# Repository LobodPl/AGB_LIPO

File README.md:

# README AGB_LIPO from makhowastaken

LiPo adapter for Game Boy Advance.

* Uses these battery terminals: https://www.aliexpress.com/item/32946601230.html
* a standard TP4056 module (Micro USB or USB C): https://www.aliexpress.com/item/32649780468.html
* and pretty much whatever diode you can get your hands on: https://www.aliexpress.com/item/32664545131.html

I got my boards in and had to make some alterations to get them to fit better. I'm still waiting on the terminals so I'll add a youtube video for instruction when I get everything in.
# My Project README

## Order at OSHPARK: https://oshpark.com/shared_projects/AJPIjHIz

## Front:

* Solder TP1 to VIN+ of TP4056
## Back:

# Symbols
* U1 - TP4056(Have to be soldered UpsideDown)
  https://aliexpress.com/item/32649780468.html (0,41$)
* U2 - TPS3700DDCR (Texas Intruments)
  https://mouser.com/ProductDetail/Texas-Instruments/TPS3700DDCR?qs=mNuCSSXMdBz5rDLbdTsfrQ%3D%3D (1,79$)
* IC1 - LP38693MP-ADJ (Texas Intruments)
  https://mouser.com/ProductDetail/Texas-Instruments/LP38693MP-ADJ-NOPB?qs=%2Fha2pyFaduhxATx%252BYNp3uIz3XjGhpXqCpbQ80pAe8SqAsUaeuhDVzOCKiaIvHl6%2F (1,45$)
* D1,D2 - SS14 Schottky Diode (or silmilar schottky diode)
  https://mouser.com/ProductDetail/ON-Semiconductor-Fairchild/SS14?qs=mVVXn4M53U%252BvrBaFv5vr4w%3D%3D (0,76$)
* C1,C2,C3 - 10u CERAMIC(0603)
  https://mouser.com/ProductDetail/Taiyo-Yuden/JMK107ABJ106KAHT?qs=sGAEpiMZZMuMW9TJLBQkXhrP50NC0Yj7qpkxl5d0wRM%3D (1$)
* C4 - 220u TANTALUM(KEMET-B)
  https://mouser.com/ProductDetail/Vishay-Sprague/TR3B106K010C1000?qs=l4Gc20tDgJLwalMJRLTcCw%3D%3D (1,08$)
* R1 - 470K(0603)
  https://mouser.com/ProductDetail/Panasonic/ERJ-UP3J474V?qs=sGAEpiMZZMtlubZbdhIBINZyO39%252BOXIfR2tJtCQBH%2FQ%3D (0,18$)
* R2 - 62K(0805)
  https://mouser.com/ProductDetail/Panasonic/ERJ-6RBD6202V?qs=sGAEpiMZZMtlubZbdhIBIAseYdsNAjdpz1c9XO5OoSg%3D (0,14$)
* R3 - 1M(0603)
  https://mouser.com/ProductDetail/Panasonic/ERJ-UP3D1004V?qs=sGAEpiMZZMtlubZbdhIBINZyO39%252BOXIfwSlLGtGqBNU%3D (0,35$)
* R4,R5 - 240K(0805)
  https://mouser.com/ProductDetail/Panasonic/ERJ-PB6B2403V?qs=sGAEpiMZZMtlubZbdhIBIMNI7sOfyRuJn5D0R%252BVWI38%3D (0,72$)
* BT1 - 103048 LiPo Cell
  https://pl.aliexpress.com/item/33000132990.html (3$)
# Cost

  PCB manufacturing costs: **2$** on JLCPCB or **9$** on OSHPARK.
  
  This project with **JLCPCB** will cost you ~13$.
  
  With **OSHPARK** you will pay ~20$.

# My Changes

* Load Sharing.
* Voltage Regulation to 3V.
* GBA Low Battery Light trigered at LiPo 3,4V.

# CHANGELOG
## >28.04.2020
* Base concept.

## 28.04.2020
* Added 3.3V Regulator.

## 29.04.2020
* Fixed Regulator capacitors.

## 01.05.2020
* Full circuit redesign.

## 01.06.2020
* One more full circuit redesign.

## 17.06.2020
* Finall release. PCB is now working corectly.

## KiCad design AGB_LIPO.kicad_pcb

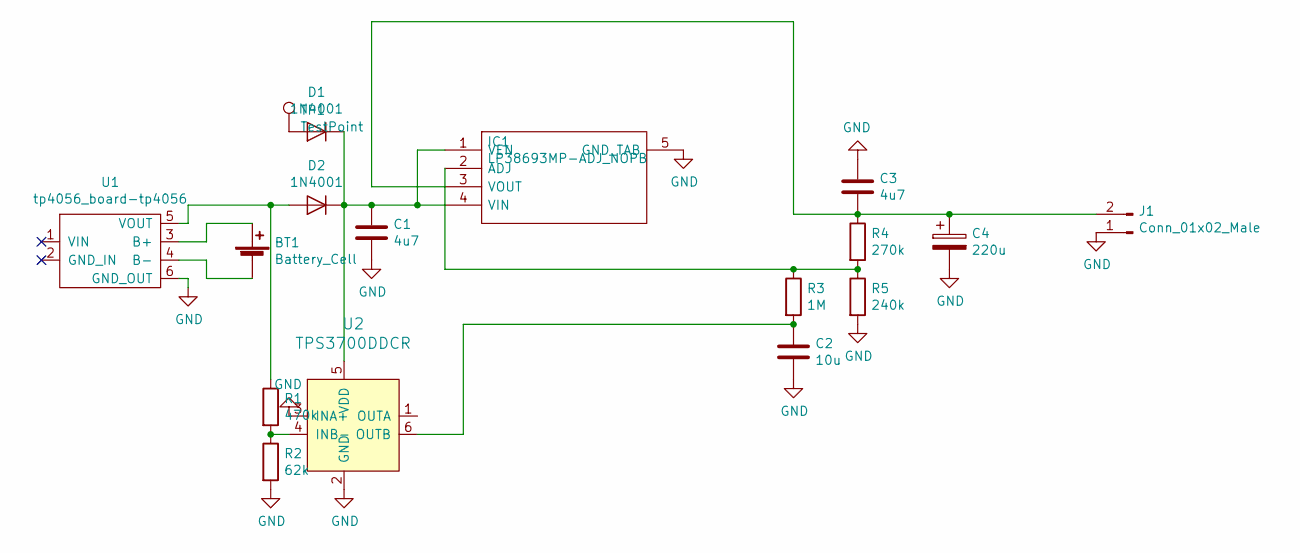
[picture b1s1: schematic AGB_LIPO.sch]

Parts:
BT1: Battery_Cell; PinHeader_1x02_P2.54mm_Vertical
C1, C3: 4u7; C_0603_1608Metric_Pad1.05x0.95mm_HandSolder
C2: 10u; C_0603_1608Metric_Pad1.05x0.95mm_HandSolder
C4: 220u; CP_EIA-3528-21_Kemet-B_Pad1.50x2.35mm_HandSolder
D1, D2: 1N4001; DIOM5626X245N
IC1: LP38693MP-ADJ_NOPB; SOT150P700X180-5N; Manufacturer_Part_Number LP38693MP-ADJ/NOPB; Mouser Part Number 926-LP38693MPADJNOPB
J1: Conn_01x02_Male; TestPoint_2Pads_Pitch2.54mm_Drill0.8mm
R1: 470k; R_0603_1608Metric_Pad1.05x0.95mm_HandSolder
R2: 62k; R_0805_2012Metric_Pad1.15x1.40mm_HandSolder
R3: 1M; R_0603_1608Metric_Pad1.05x0.95mm_HandSolder
R4: 270k; R_0805_2012Metric_Pad1.15x1.40mm_HandSolder
R5: 240k; R_0805_2012Metric_Pad1.15x1.40mm_HandSolder
TP1: TestPoint; TestPoint_Loop_D1.80mm_Drill1.0mm_Beaded
U1: tp4056_board-tp4056; 4056E_LiIon_loader
U2: TPS3700DDCR; SOT98P280X110-6N; MPN TPS3700DDCR; Digi-Key_PN 296-30395-1-ND

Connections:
GND: C1.2, C2.2, C3.1, C4.2, IC1.5 (GND_TAB), J1.1, R2.2, R5.2, U1.6 (GND_OUT), U2.2 (GND), U2.3 (INA+)
unnamed: BT1.1 (+), U1.3 (B+)
unnamed: BT1.2 (-), U1.4 (B-)
unnamed: C1.1, D1.1 (K), D2.1 (K), IC1.1 (VEN), IC1.4 (VIN), U2.5 (VDD)
unnamed: C2.1, R3.2, U2.6 (OUTB)
unnamed: C3.2, C4.1, IC1.3 (VOUT), J1.2, R4.1
unnamed: D1.2 (A), TP1.1
unnamed: D2.2 (A), R1.1, U1.5 (VOUT)
unnamed: IC1.2 (ADJ), R3.1, R4.2, R5.1
unnamed: R1.2, R2.1, U2.4 (INB-)

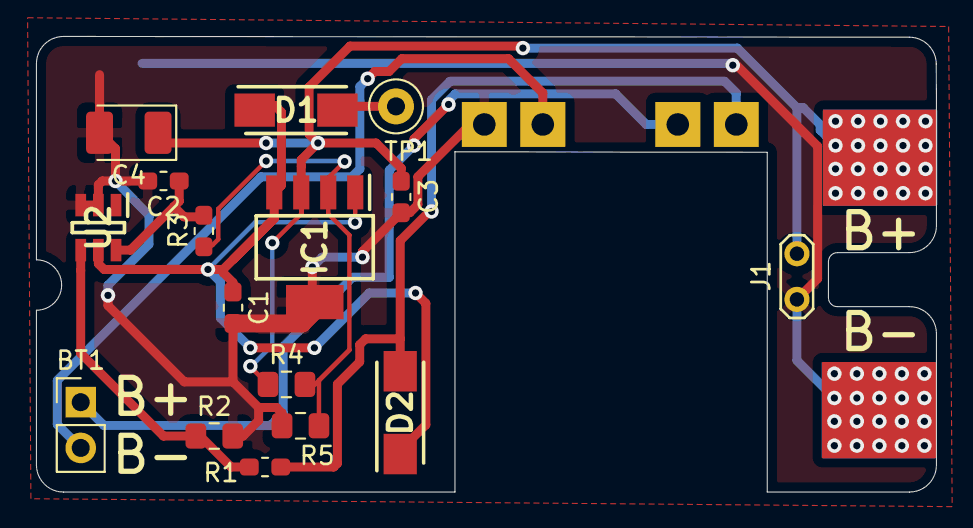
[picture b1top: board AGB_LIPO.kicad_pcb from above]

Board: 2 copper layers, 50.0 x 25.3 mm, 17 parts (1 on the bottom side), 10 nets.

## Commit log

2020-04-26 Load Sharing and Voltage stabilizer
2020-04-26 updated images
2020-04-26 Board updated
2020-04-26 Updated IMG's
2020-04-29 29/04 Update
2020-04-29 29/04 Updated photos
2020-04-29 29/04 Symbol fix
2020-05-01 Full Circuit redesign
2020-05-01 01/05 Full Circuit redesign README FIX
2020-06-17 17.06 UPDATE
2020-06-17 17.06 UPDATE 2
